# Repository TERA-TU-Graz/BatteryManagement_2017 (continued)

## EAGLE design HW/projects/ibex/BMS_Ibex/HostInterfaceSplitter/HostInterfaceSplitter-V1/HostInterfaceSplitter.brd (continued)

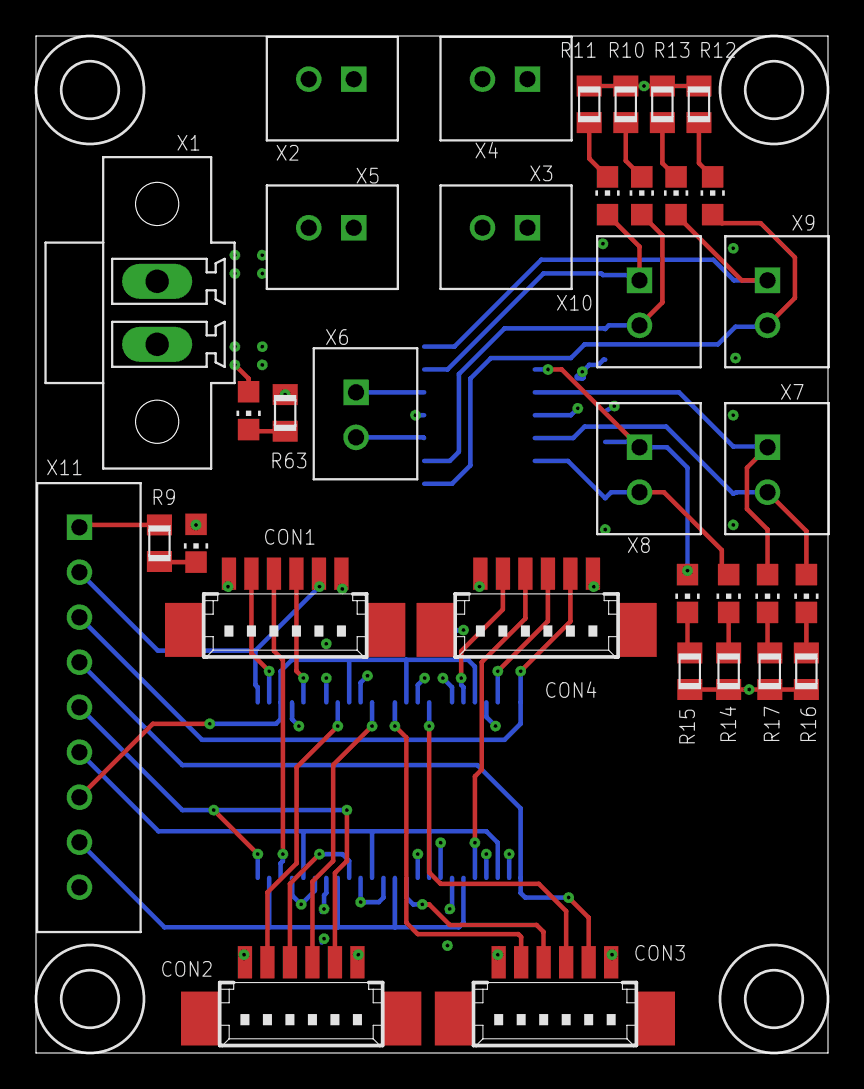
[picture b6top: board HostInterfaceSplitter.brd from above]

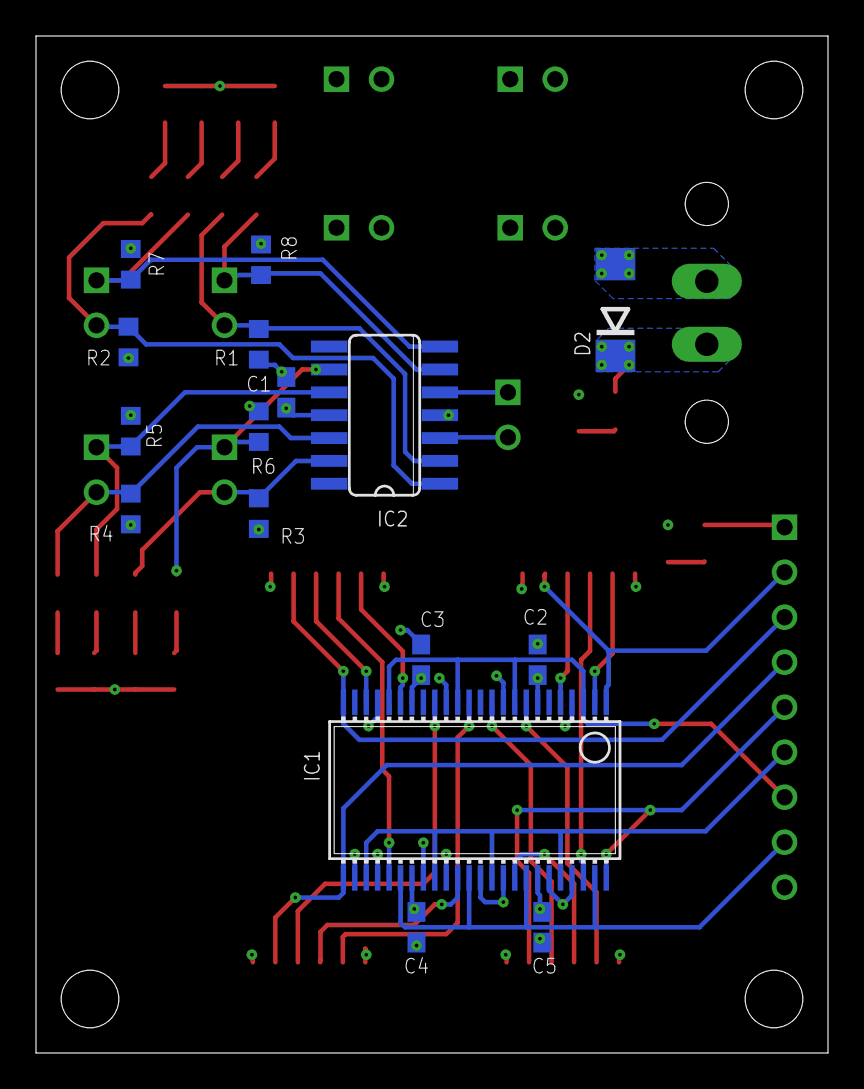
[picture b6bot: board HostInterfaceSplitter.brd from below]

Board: 4 copper layers, 44.0 x 56.5 mm, 55 parts (16 on the bottom side), 42 nets.
